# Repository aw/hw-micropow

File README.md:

# μPow: 3D printer buck converter for 12V/5V fans

A dual-output switching DC-DC buck converter to replace the 24V fans on a 3D printer.

This project is also described in detail [on Hackaday.io](https://hackaday.io/project/179566-pow-3d-printer-buck-converter-for-12v5v-fans)

This project is [certified open hardware](https://certification.oshwa.org/jp000010.html):

# How it works

The left side of the PCB accepts 8V to 28V DC input. It then converts the input voltage to 12V and then to 5V.

The output voltages are accessible on the right side of the PCB and can be used to power 12V or 5V fans or other devices.

# PCB features

  * Form factor 44mm x 22mm
  * PCB traces are 1mm and should handle at least 1.5A of current
  * Open Source Hardware under [CC BY-SA 4.0](#License)
  * On-board (SMD) capacitors, fuses, and diodes
  * Simple passive design draws 0mA current when no devices are connected
  * Thermal vias in strategic locations

# BOM (through-hole)

| Quantity | Item and Description | Datasheet |
| :----: | :---- | :---- |
| 1 | XPPower VR10S05 SIP3 5V 1A DC-DC switching regulator | [XPPower-VR10-1A-voltage-regulator.pdf](datasheets/XPPower-VR10-1A-voltage-regulator.pdf) |
| 1 | XPPower VR10S12 SIP3 12V 1A DC-DC switching regulator | [XPPower-VR10-1A-voltage-regulator.pdf](datasheets/XPPower-VR10-1A-voltage-regulator.pdf) |
| 3 | 3-pin JST-XH male connectors | |

# BOM (surface mount)

| Quantity | Item and Description |
| :----: | :---- |
| 1 | 10uF 50V Capacitor 5x5.3mm |
| 2 | 22uF 16V Capacitors 5x5.3mm |
| 1 | 40V 1A Diode SOD-123 |
| 2 | 28V 1A Diode SOD-123 |
| 1 | 33V 1.1A/2.2A Polyfuse 1812 |

# Schematic

The schematic is available [here](schematic-v1.pdf)

# Notes

This PCB was designed with [Kicad](https://kicad.org/) v5.1.9 from the `debian buster-backports` repository.

I take no responsibility for any problems that may occur with your use of this PCB or design files. Create and use at your own risk.

# License

μPow: 3D printer buck converter for 12V/5V fans © 2021 by [Alexander Williams](https://a1w.ca/) is licensed under [_CC BY-SA 4.0_ (Attribution-ShareAlike 4.0 International)](https://creativecommons.org/licenses/by-sa/4.0/).

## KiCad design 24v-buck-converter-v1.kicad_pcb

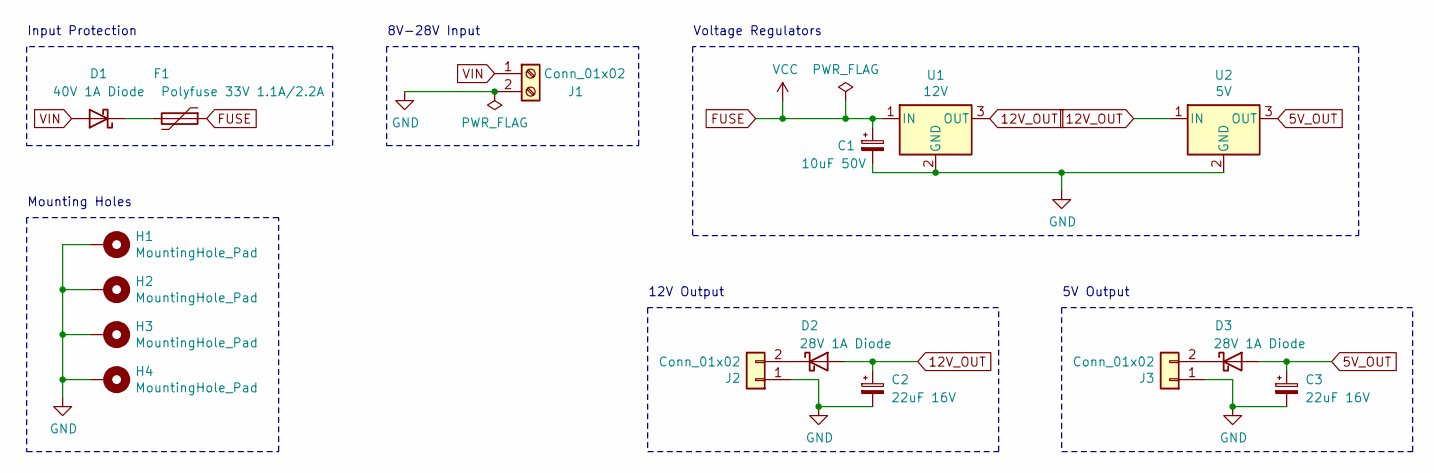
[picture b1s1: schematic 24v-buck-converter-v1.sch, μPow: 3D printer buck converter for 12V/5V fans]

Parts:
C1: 10uF 50V; CP_Elec_5x5.3; LCSC C249452
C2, C3: 22uF 16V; CP_Elec_5x5.3; LCSC C249477
D1: 40V 1A Diode; D_SOD-123; LCSC C8598
D2, D3: 28V 1A Diode; D_SOD-123; LCSC C8598
F1: Polyfuse 33V 1.1A/2.2A; Fuse_1812_4532Metric_Pad1.30x3.40mm_HandSolder; LCSC C369173
H1, H2, H3, H4: MountingHole_Pad; MountingHole_2.7mm_M2.5_Pad_Via
J1, J2, J3: Conn_01x02; JST_XH_B2B-XH-A_1x02_P2.50mm_Vertical
U1: 12V; Converter_DCDC_RECOM_R-78E-0.5_THT
U2: 5V; Converter_DCDC_RECOM_R-78E-0.5_THT

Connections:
5V_OUT: C3.1, D3.2 (A), U2.3 (OUT)
12V_OUT: C2.1, D2.2 (A), U1.3 (OUT), U2.1 (IN)
FUSE: C1.1, F1.1, U1.1 (IN)
GND: C1.2, C2.2, C3.2, H1.1, H2.1, H3.1, H4.1, J1.2, J2.1, J3.1, U1.2 (GND), U2.2 (GND)
unnamed: D1.1 (K), F1.2
unnamed: D2.1 (K), J2.2
unnamed: D3.1 (K), J3.2
VIN: D1.2 (A), J1.1

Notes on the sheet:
Mounting Holes
Voltage Regulators
Input Protection
8V-28V Input
12V Output
5V Output

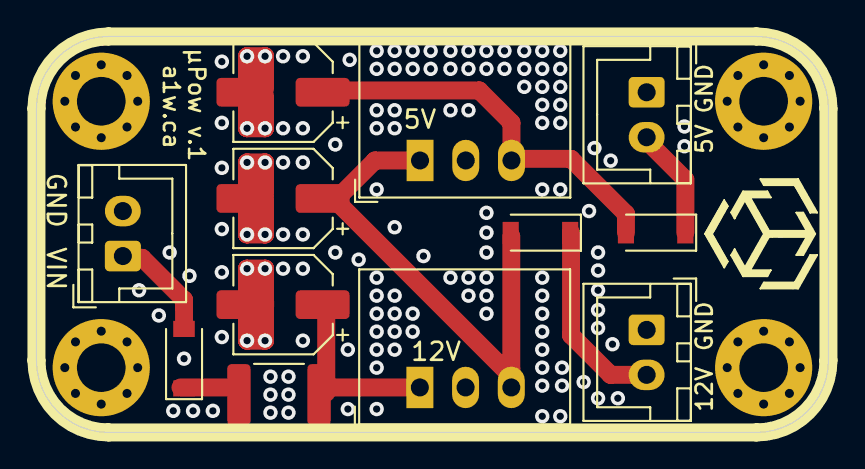
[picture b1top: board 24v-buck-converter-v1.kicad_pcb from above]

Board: 2 copper layers, 44.0 x 22.0 mm, 16 parts (0 on the bottom side), 8 nets.

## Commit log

2021-08-05 Add README and LICENSE
2021-08-05 Add design files
2021-08-10 Change license to CC BY-SA 4.0
2021-08-10 Update license and URL in schematic
2021-08-10 Ensure logo and modules are included
2021-08-12 Add certified OSHWA open hardware logo
2021-08-12 Update BOM and upload datasheets
2021-08-12 Fix link to PDF in BOM

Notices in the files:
24v-buck-converter-v1.sch:
License: CC BY-SA 4.0
